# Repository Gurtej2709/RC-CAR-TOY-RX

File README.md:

# RC-CAR-TOY-RX
A custom-designed Receiver (RX) PCB for an RC car toy, developed using KiCad. The board is designed to receive wireless control signals from the transmitter and interface with the RC car's motor/control circuitry.

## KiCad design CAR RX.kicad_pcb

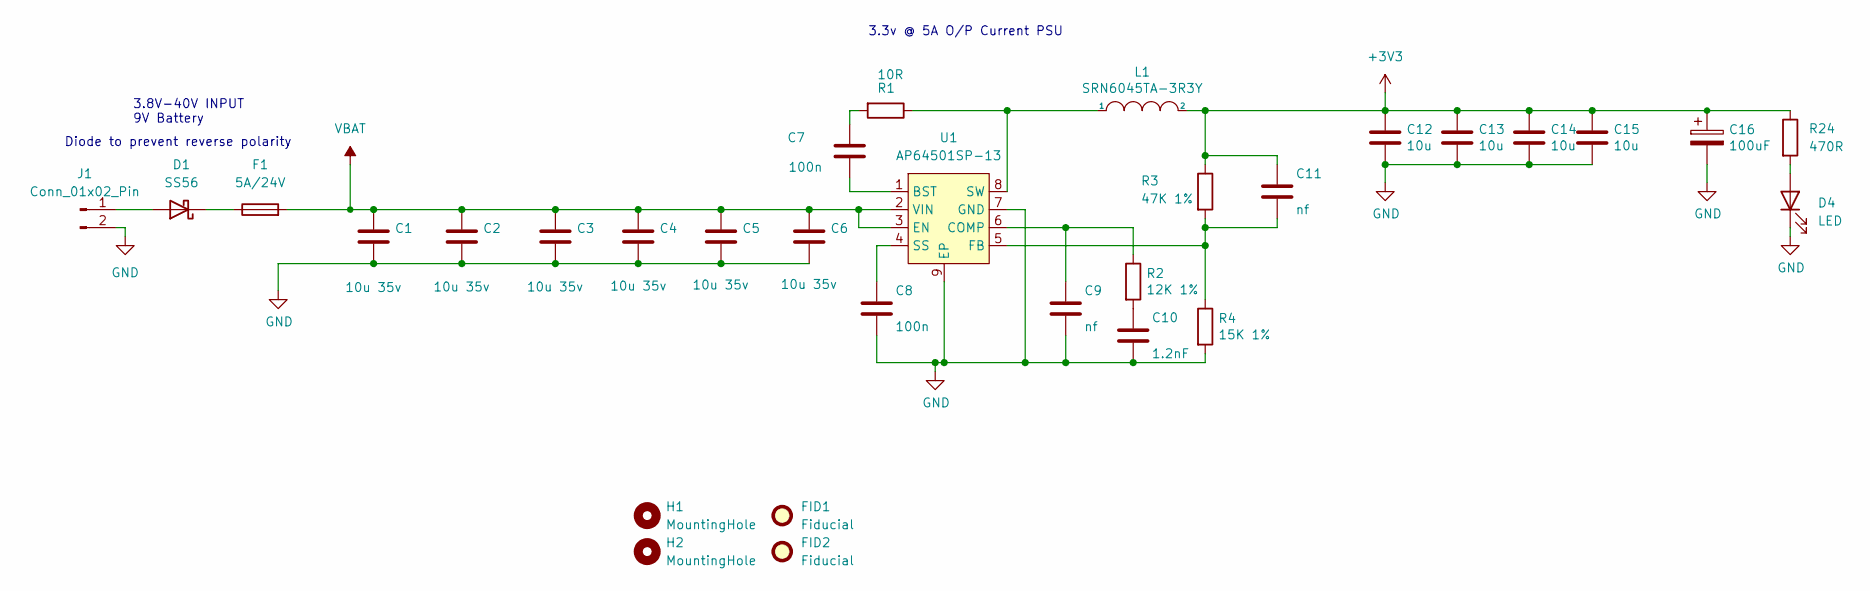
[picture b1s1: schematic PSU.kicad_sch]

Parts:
C1, C2, C3, C4, C5, C6: 10u 35v; C_0805_2012Metric; Part Description 10uF 10% or 20% 35V Ceramic Capacitor X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
C7, C8: 100n; C_0402_1005Metric; Part Description 0.1uF 10% 16V Ceramic Capacitor X7R 040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
C9: nf; C_0402_1005Metric
C10: 1.2nF; C_0402_1005Metric; Part Description 1200pF 10% 10V Ceramic Capacitor X5R 04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
C11: nf; C_0402_1005Metric; Part Description 27pF 5% 50V Ceramic Capacitor C0G, NP0 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
C12, C13, C14, C15: 10u; C_0805_2012Metric; Part Description 10uF 10% 10V Ceramic Capacitor X7R 0805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
C16: 100uF; CP_EIA-7343-31_Kemet-D; Part Description Capacitor, SP-Cap, 100u, 6.3V, 15mR ESR
D1: SS56; D_SMC
D4: LED; LED_0603_1608Metric_Pad1.05x0.95mm_HandSolder
F1: 5A/24V; Fuse_2512_6332Metric_Pad1.52x3.35mm_HandSolder
FID1, FID2: Fiducial; Fiducial_1.5mm_Mask3mm
H1, H2: MountingHole; MountingHole_3.2mm_M3_DIN965_Pad
J1: Conn_01x02_Pin; PinHeader_1x02_P2.54mm_Vertical
L1: SRN6045TA-3R3Y; L_Bourns_SRN6045TA; Part Description 3.3µH Semi-Shielded Wirewound Inductor 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
R1: 10R; R_0402_1005Metric; Part Description Resistor 10R M1005 1% 63mW
R2: 12K 1%; R_0402_1005Metric; Part Description Resistor 12K M1005 1% 63mW
R3: 47K 1%; R_0402_1005Metric; Part Description Resistor 47K M1005 1% 63mW
R4: 15K 1%; R_0402_1005Metric; Part Description Resistor 15K M1005 1% 63mW
R24: 470R; R_0603_1608Metric_Pad0.98x0.95mm_HandSolder
U1: AP64501SP-13; SOIC-8-1EP_3.9x4.9mm_P1.27mm_EP2.95x4.9mm_Mask2.71x3.4mm_Th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

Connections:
+3V3: C11.1, C12.1, C13.1, C14.1, C15.1, C16.1, L1.2, R3.1, R24.1; also elsewhere on the board
GND: C1.2, C2.2, C3.2, C4.2, C5.2, C6.2, C8.2, C9.2, C10.2, C12.2, C13.2, C14.2, C15.2, C16.2, D4.1 (K), J1.2, R4.2, U1.7 (GND), U1.9 (EP); also elsewhere on the board
unnamed: C7.1, R1.2
unnamed: C10.1, R2.2
unnamed: D1.2 (A), J1.1
unnamed: D1.1 (K), F1.1
unnamed: D4.2 (A), R24.2
unnamed: C7.2, U1.1 (BST)
unnamed: C9.1, R2.1, U1.6 (COMP)
unnamed: C11.2, R3.2, R4.1, U1.5 (FB)
unnamed: C8.1, U1.4 (SS)
unnamed: L1.1, R1.1, U1.8 (SW)
VBAT: C1.1, C2.1, C3.1, C4.1, C5.1, C6.1, F1.2, U1.2 (VIN), U1.3 (EN)

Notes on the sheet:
3.8V-40V INPUT 9V Battery
3.3v @ 5A O/P Current PSU
Diode to prevent reverse polarity

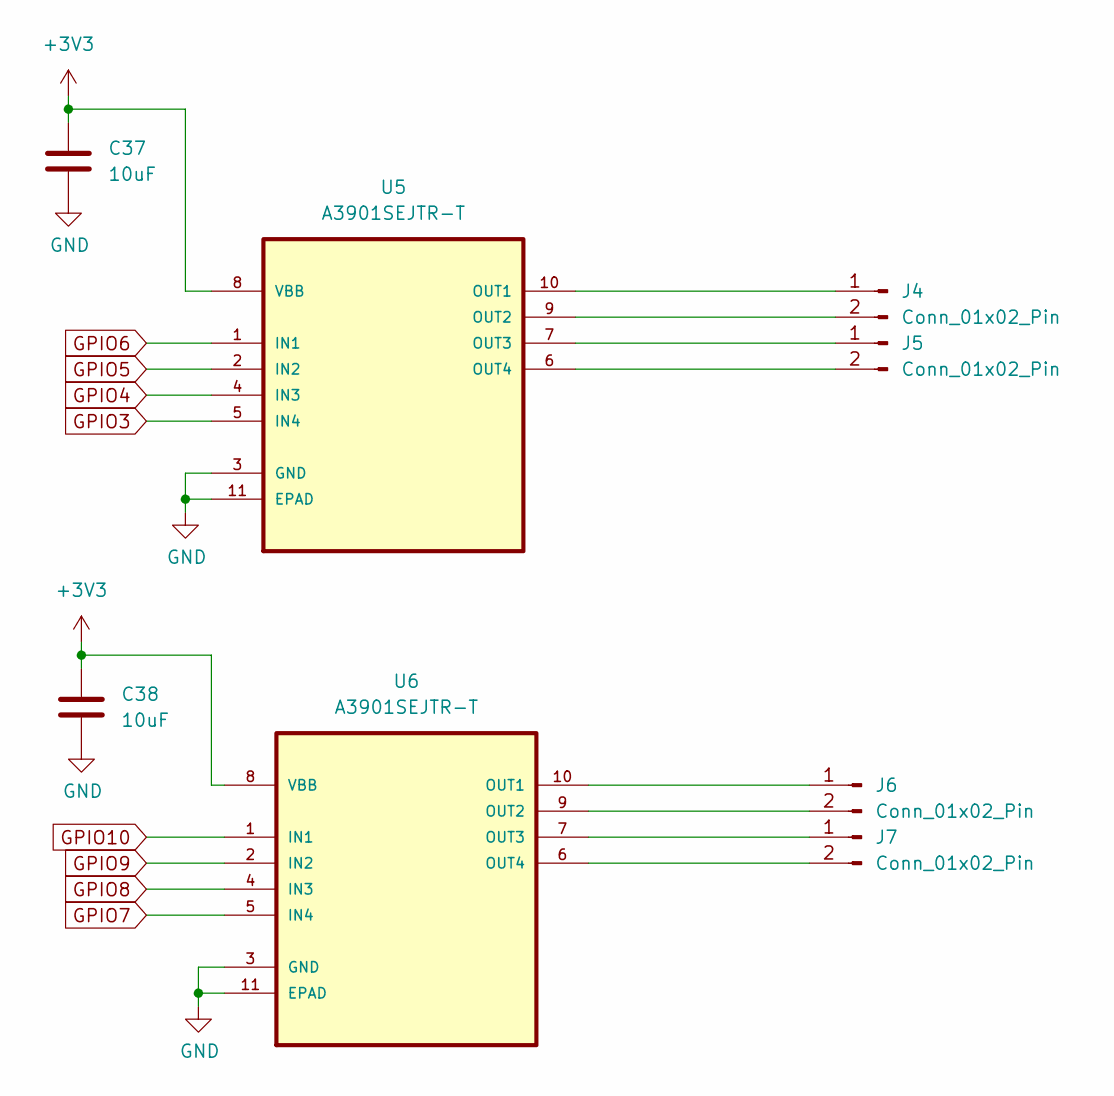
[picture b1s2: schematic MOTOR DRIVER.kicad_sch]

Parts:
C37, C38: 10uF; C_1206_3216Metric_Pad1.33x1.80mm_HandSolder
J4, J5, J6, J7: Conn_01x02_Pin; PinHeader_1x02_P2.54mm_Vertical
U5, U6: A3901SEJTR-T; DFN300X300X75-11N; MPN A3901SEJTR-T

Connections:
+3V3: C37.1, C38.1, U5.8 (VBB), U6.8 (VBB); also elsewhere on the board
GND: C37.2, C38.2, U5.3 (GND), U5.11 (EPAD), U6.3 (GND), U6.11 (EPAD); also elsewhere on the board
GPIO3: U5.5 (IN4); also elsewhere on the board
GPIO4: U5.4 (IN3); also elsewhere on the board
GPIO5: U5.2 (IN2); also elsewhere on the board
GPIO6: U5.1 (IN1); also elsewhere on the board
GPIO7: U6.5 (IN4); also elsewhere on the board
GPIO8: U6.4 (IN3); also elsewhere on the board
GPIO9: U6.2 (IN2); also elsewhere on the board
GPIO10: U6.1 (IN1); also elsewhere on the board
unnamed: J4.1, U5.10 (OUT1)
unnamed: J4.2, U5.9 (OUT2)
unnamed: J5.1, U5.7 (OUT3)
unnamed: J5.2, U5.6 (OUT4)
unnamed: J6.1, U6.10 (OUT1)
unnamed: J6.2, U6.9 (OUT2)
unnamed: J7.1, U6.7 (OUT3)
unnamed: J7.2, U6.6 (OUT4)

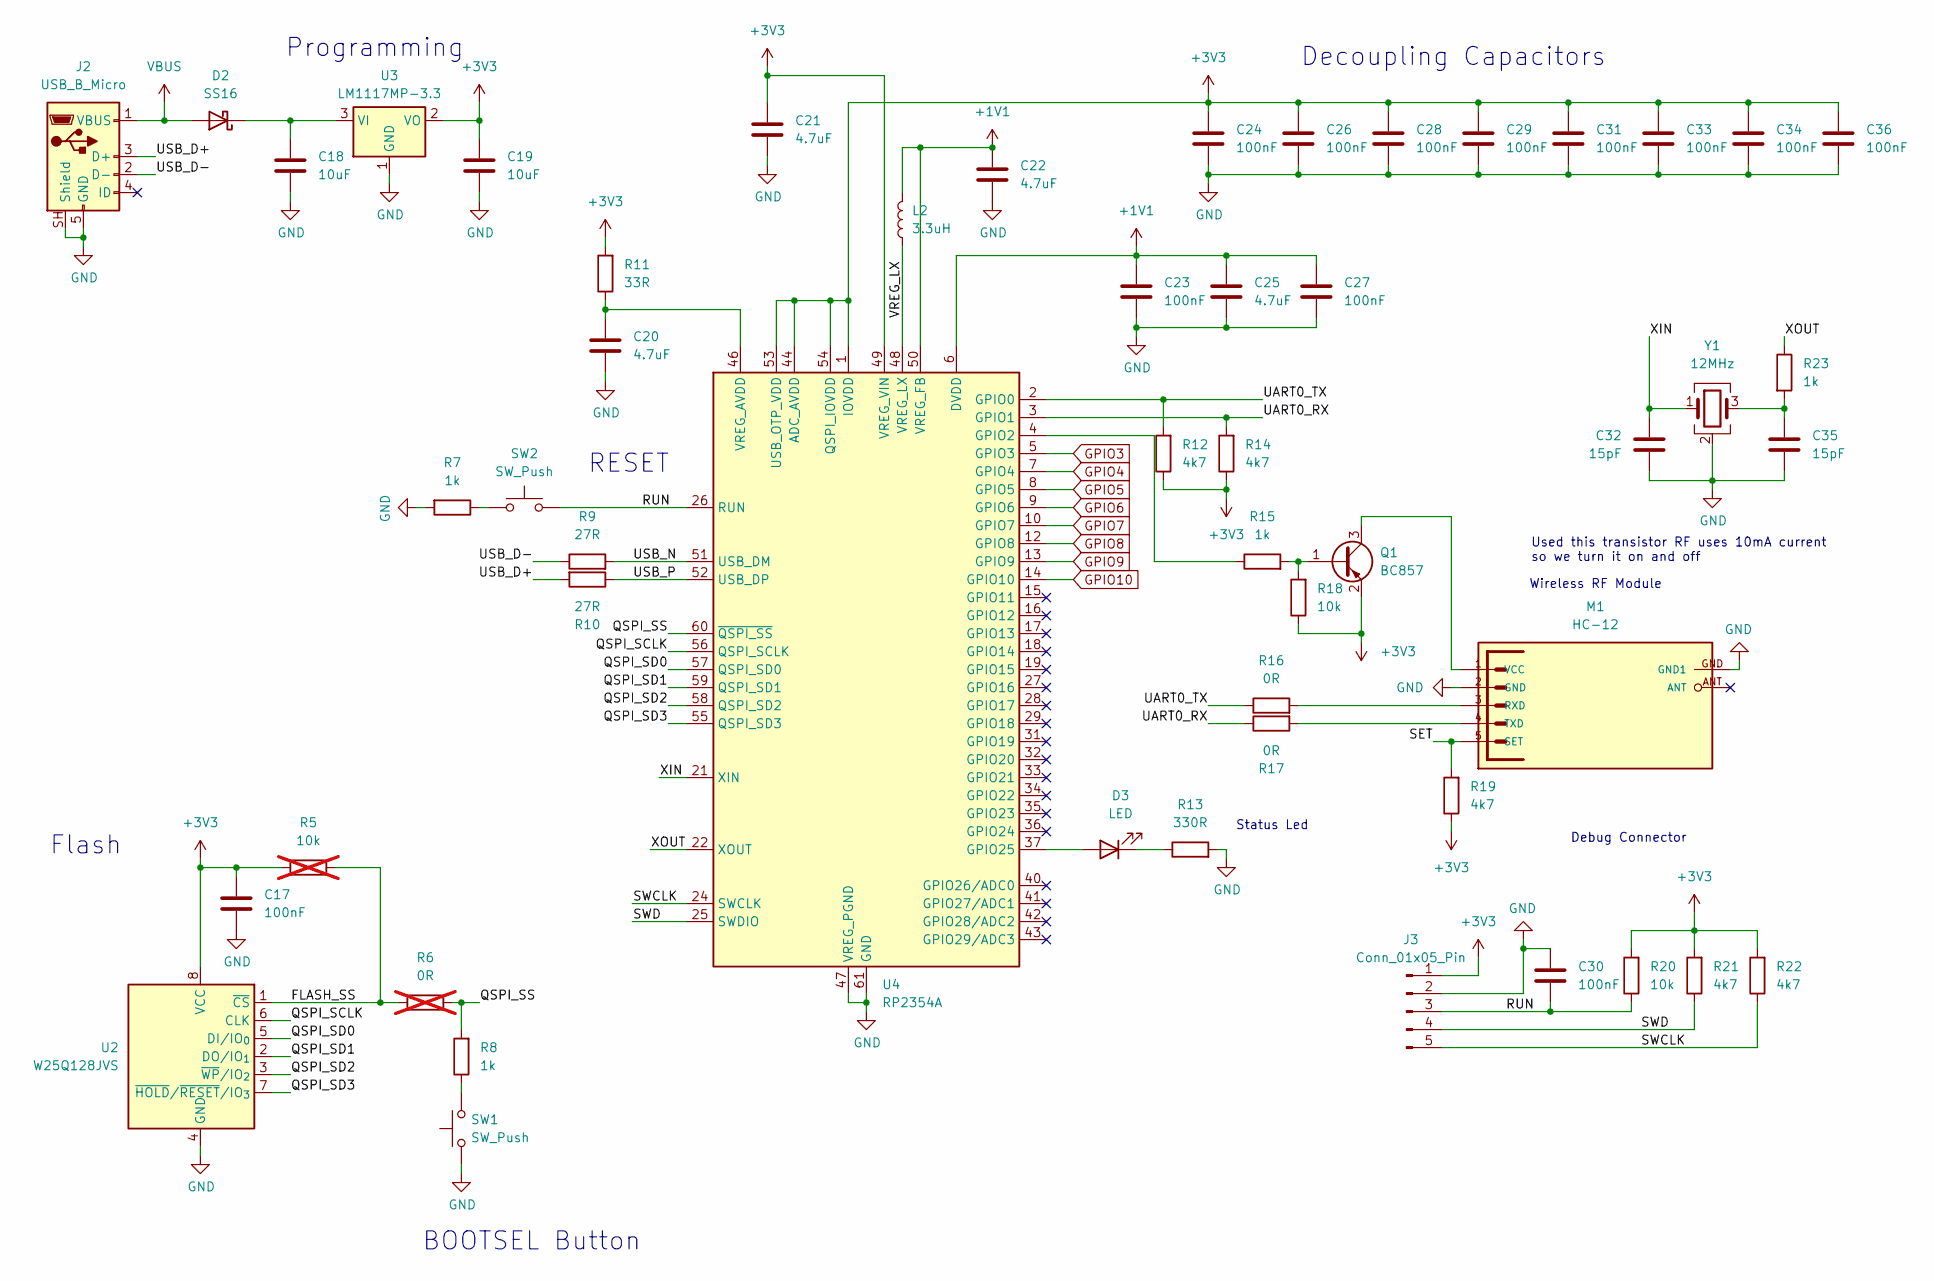
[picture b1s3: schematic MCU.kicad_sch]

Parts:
C17, C23, C24, C26, C27, C28, C29, C30, C31, C33, C34, C36: 100nF; C_0603_1608Metric_Pad1.08x0.95mm_HandSolder
C18, C19: 10uF; C_1206_3216Metric_Pad1.33x1.80mm_HandSolder
C20, C21, C22, C25: 4.7uF; C_0603_1608Metric_Pad1.08x0.95mm_HandSolder
C32, C35: 15pF; C_0603_1608Metric_Pad1.08x0.95mm_HandSolder
D2: SS16; D_SMA
D3: LED; LED_0603_1608Metric_Pad1.05x0.95mm_HandSolder
J2: USB_B_Micro; USB_Micro-B_Amphenol_10103594-0001LF_Horizontal
J3: Conn_01x05_Pin; PinHeader_1x05_P2.54mm_Vertical
L2: 3.3uH; L_1008_2520Metric_Pad1.43x2.20mm_HandSolder
M1: HC-12
Q1: BC857; SOT-23
R5: 10k; R_0603_1608Metric_Pad0.98x0.95mm_HandSolder; not fitted
R6: 0R; R_0603_1608Metric_Pad0.98x0.95mm_HandSolder; not fitted
R7, R8, R15, R23: 1k; R_0603_1608Metric_Pad0.98x0.95mm_HandSolder
R9, R10: 27R; R_0603_1608Metric_Pad0.98x0.95mm_HandSolder
R11: 33R; R_0603_1608Metric_Pad0.98x0.95mm_HandSolder
R12, R14, R19, R21, R22: 4k7; R_0603_1608Metric_Pad0.98x0.95mm_HandSolder
R13: 330R; R_0603_1608Metric_Pad0.98x0.95mm_HandSolder
R16, R17: 0R; R_0603_1608Metric_Pad0.98x0.95mm_HandSolder
R18, R20: 10k; R_0603_1608Metric_Pad0.98x0.95mm_HandSolder
SW1, SW2: SW_Push; SW_SPST_B3SL-1022P
U2: W25Q128JVS; SOIC-8_5.3x5.3mm_P1.27mm
U3: LM1117MP-3.3; SOT-223-3_TabPin2
U4: RP2354A; QFN-60-1EP_7x7mm_P0.4mm_EP3.4x3.4mm_ThermalVias
Y1: 12MHz; Crystal_SMD_SeikoEpson_FA238-4Pin_3.2x2.5mm

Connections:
+1V1: C22.1, C23.1, C25.1, C27.1, L2.2, U4.6 (DVDD), U4.23 (DVDD), U4.39 (DVDD), U4.50 (VREG_FB)
+3V3: C17.1, C19.1, C21.1, C24.1, C26.1, C28.1, C29.1, C31.1, C33.1, C34.1, C36.1, J3.1, Q1.2 (E), R5.1, R11.2, R12.1, R14.1, R18.1, R19.1, R20.2, R21.2, R22.2, U2.8 (VCC), U3.2 (VO), U4.1 (IOVDD), U4.11 (IOVDD), U4.20 (IOVDD), U4.30 (IOVDD), U4.38 (IOVDD), U4.44 (ADC_AVDD), U4.45 (IOVDD), U4.49 (VREG_VIN), U4.53 (USB_OTP_VDD), U4.54 (QSPI_IOVDD); also elsewhere on the board
/MCU/FLASH_SS: R5.2, R6.1, U2.1 (~CS)
/MCU/QSPI_SCLK: U2.6 (CLK), U4.56 (QSPI_SCLK)
/MCU/QSPI_SD0: U2.5 (DI/IO_{0}), U4.57 (QSPI_SD0)
/MCU/QSPI_SD1: U2.2 (DO/IO_{1}), U4.59 (QSPI_SD1)
/MCU/QSPI_SD2: U2.3 (~WP/IO_{2}), U4.58 (QSPI_SD2)
/MCU/QSPI_SD3: U2.7 (~HOLD/~RESET/IO_{3}), U4.55 (QSPI_SD3)
/MCU/QSPI_SS: R6.2, R8.2, U4.60 (~QSPI_SS)
/MCU/RUN: C30.2, J3.3, R20.1, SW2.2, U4.26 (RUN)
/MCU/SET: M1.5 (SET), R19.2
/MCU/SWCLK: J3.5, R22.1, U4.24 (SWCLK)
/MCU/SWD: J3.4, R21.1, U4.25 (SWDIO)
/MCU/UART0_RX: R14.2, R17.1, U4.3 (GPIO1)
/MCU/UART0_TX: R12.2, R16.1, U4.2 (GPIO0)
/MCU/USB_D+: J2.3 (D+), R10.2
/MCU/USB_D-: J2.2 (D-), R9.1
/MCU/USB_N: R9.2, U4.51 (USB_DM)
/MCU/USB_P: R10.1, U4.52 (USB_DP)
/MCU/VREG_LX: L2.1, U4.48 (VREG_LX)
/MCU/XIN: C32.1, U4.21 (XIN), Y1.1
/MCU/XOUT: R23.1, U4.22 (XOUT)
GND: C17.2, C18.2, C19.2, C20.2, C21.2, C22.2, C23.2, C24.2, C25.2, C26.2, C27.2, C28.2, C29.2, C30.1, C31.2, C32.2, C33.2, C34.2, C35.2, C36.2, J2.5 (GND), J2.SH (Shield), J3.2, M1.2 (GND), M1.GND (GND1), M1.GND1, R7.2, R13.2, SW1.1, U2.4 (GND), U3.1 (GND), U4.47 (VREG_PGND), U4.61 (GND), Y1.2 (G), Y1.4 (G); also elsewhere on the board
GPIO3: U4.5 (GPIO3); also elsewhere on the board
GPIO4: U4.7 (GPIO4); also elsewhere on the board
GPIO5: U4.8 (GPIO5); also elsewhere on the board
GPIO6: U4.9 (GPIO6); also elsewhere on the board
GPIO7: U4.10 (GPIO7); also elsewhere on the board
GPIO8: U4.12 (GPIO8); also elsewhere on the board
GPIO9: U4.13 (GPIO9); also elsewhere on the board
GPIO10: U4.14 (GPIO10); also elsewhere on the board
unnamed: C35.1, R23.2, Y1.3
unnamed: C18.1, D2.1 (K), U3.3 (VI)
unnamed: D3.2 (A), U4.37 (GPIO25)
unnamed: D3.1 (K), R13.1
unnamed: M1.3 (RXD), R16.2
unnamed: M1.4 (TXD), R17.2
unnamed: M1.1 (VCC), Q1.3 (C)
unnamed: Q1.1 (B), R15.2, R18.2
unnamed: R7.1, SW2.1
unnamed: R8.1, SW1.2
unnamed: R15.1, U4.4 (GPIO2)
unnamed: C20.1, R11.1, U4.46 (VREG_AVDD)
VBUS: D2.2 (A), J2.1 (VBUS)

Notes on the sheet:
Status Led
Decoupling Capacitors
Debug Connector
Used this transistor RF uses 10mA current so we turn it on and off
BOOTSEL Button
Wireless RF Module
Flash
RESET
Programming

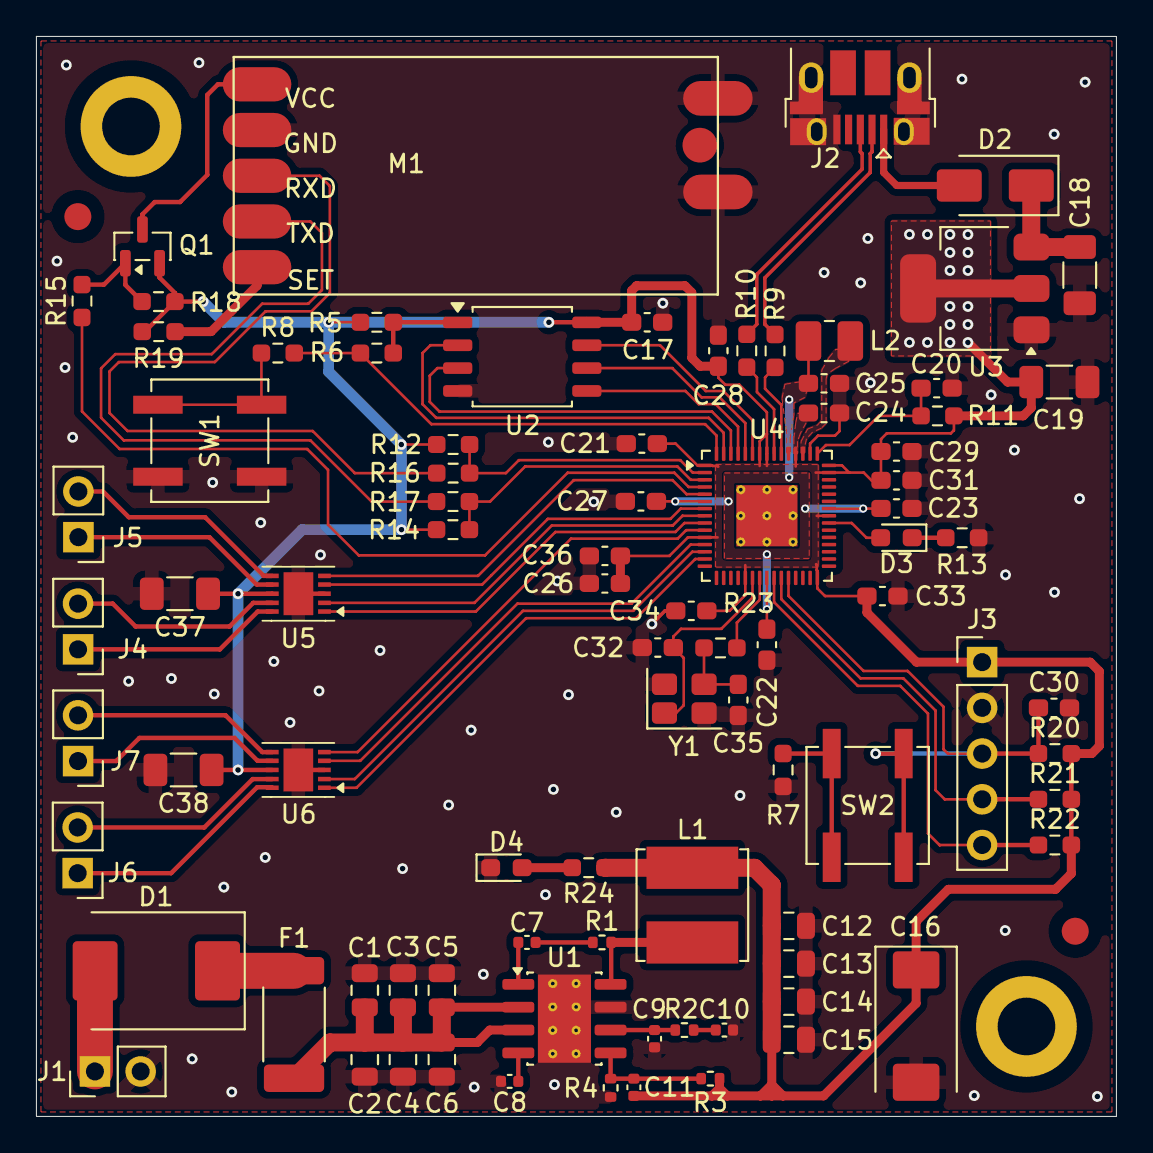
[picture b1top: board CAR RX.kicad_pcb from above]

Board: 2 copper layers, 60.0 x 60.0 mm, 91 parts (0 on the bottom side), 63 nets.
